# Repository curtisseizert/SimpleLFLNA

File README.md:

# SimpleLFLNA

This project contains design files for a low-frequency (0.1 - 10 Hz), AC-coupled low noise amplifier intended for measuring noise of voltage references, low noise linear supplies, etc. A number of other designs utilize input high pass filters with large (1 - 2.2 mF) electrolytic capacitors and low (ca. 1 k) resistors, this approach suffers from several drawbacks. Electrolytic capacitors exhibit high levels of dielectric absorption, leading to long settling times. Leakage can also be problematic and requires selection of parts to ensure that the amplifier does not saturate when DC bias is applied. Moreover, measurements of sources like unbuffered DAC outputs suffers from considerable input signal attenuation due to low input impedance in the passband. This design instead utilizes a much smaller (4.7 uF) polypropylene AC-coupling capacitor and large (10M) resistor with a hybrid JFET input amplifier to remove the DC bias from the signal of interest. Dielectric absorption and leakage for polypropylene capacitors is much lower than that of Al electrolytics, allowing faster settling and obviating part selection.

While this amplifier is yet to be built and tested, the design concept borrows heavily from another project (https://github.com/curtisseizert/LowFreqLNA). That project was aimed at lowest possible noise and greatest bandwidth, with different gain and bandwidth options accessible via front panel switches, but the resulting complexity, part count, and cost were relatively high for a DIY project. This project is a simpler and less expensive version with fixed gain and bandwidth. The board is a 4-layer 120x78 mm PCB designed to fit in a Hammond 1455K1201 enclosure. The amplifier can be powered by two 9V batteries or an external power source. The "settle" switch, which discharges the interstage HP filter capacitors and saturation indicator are reasonably simple quality of life features that were maintained from the more complex version. The expected noise floor is about 60-75 nV p-p depending upon some parts choices noted in the schematic. BOM cost is ca. $75 from Digikey.

I will update this repository with testing results once I have built a prototype.

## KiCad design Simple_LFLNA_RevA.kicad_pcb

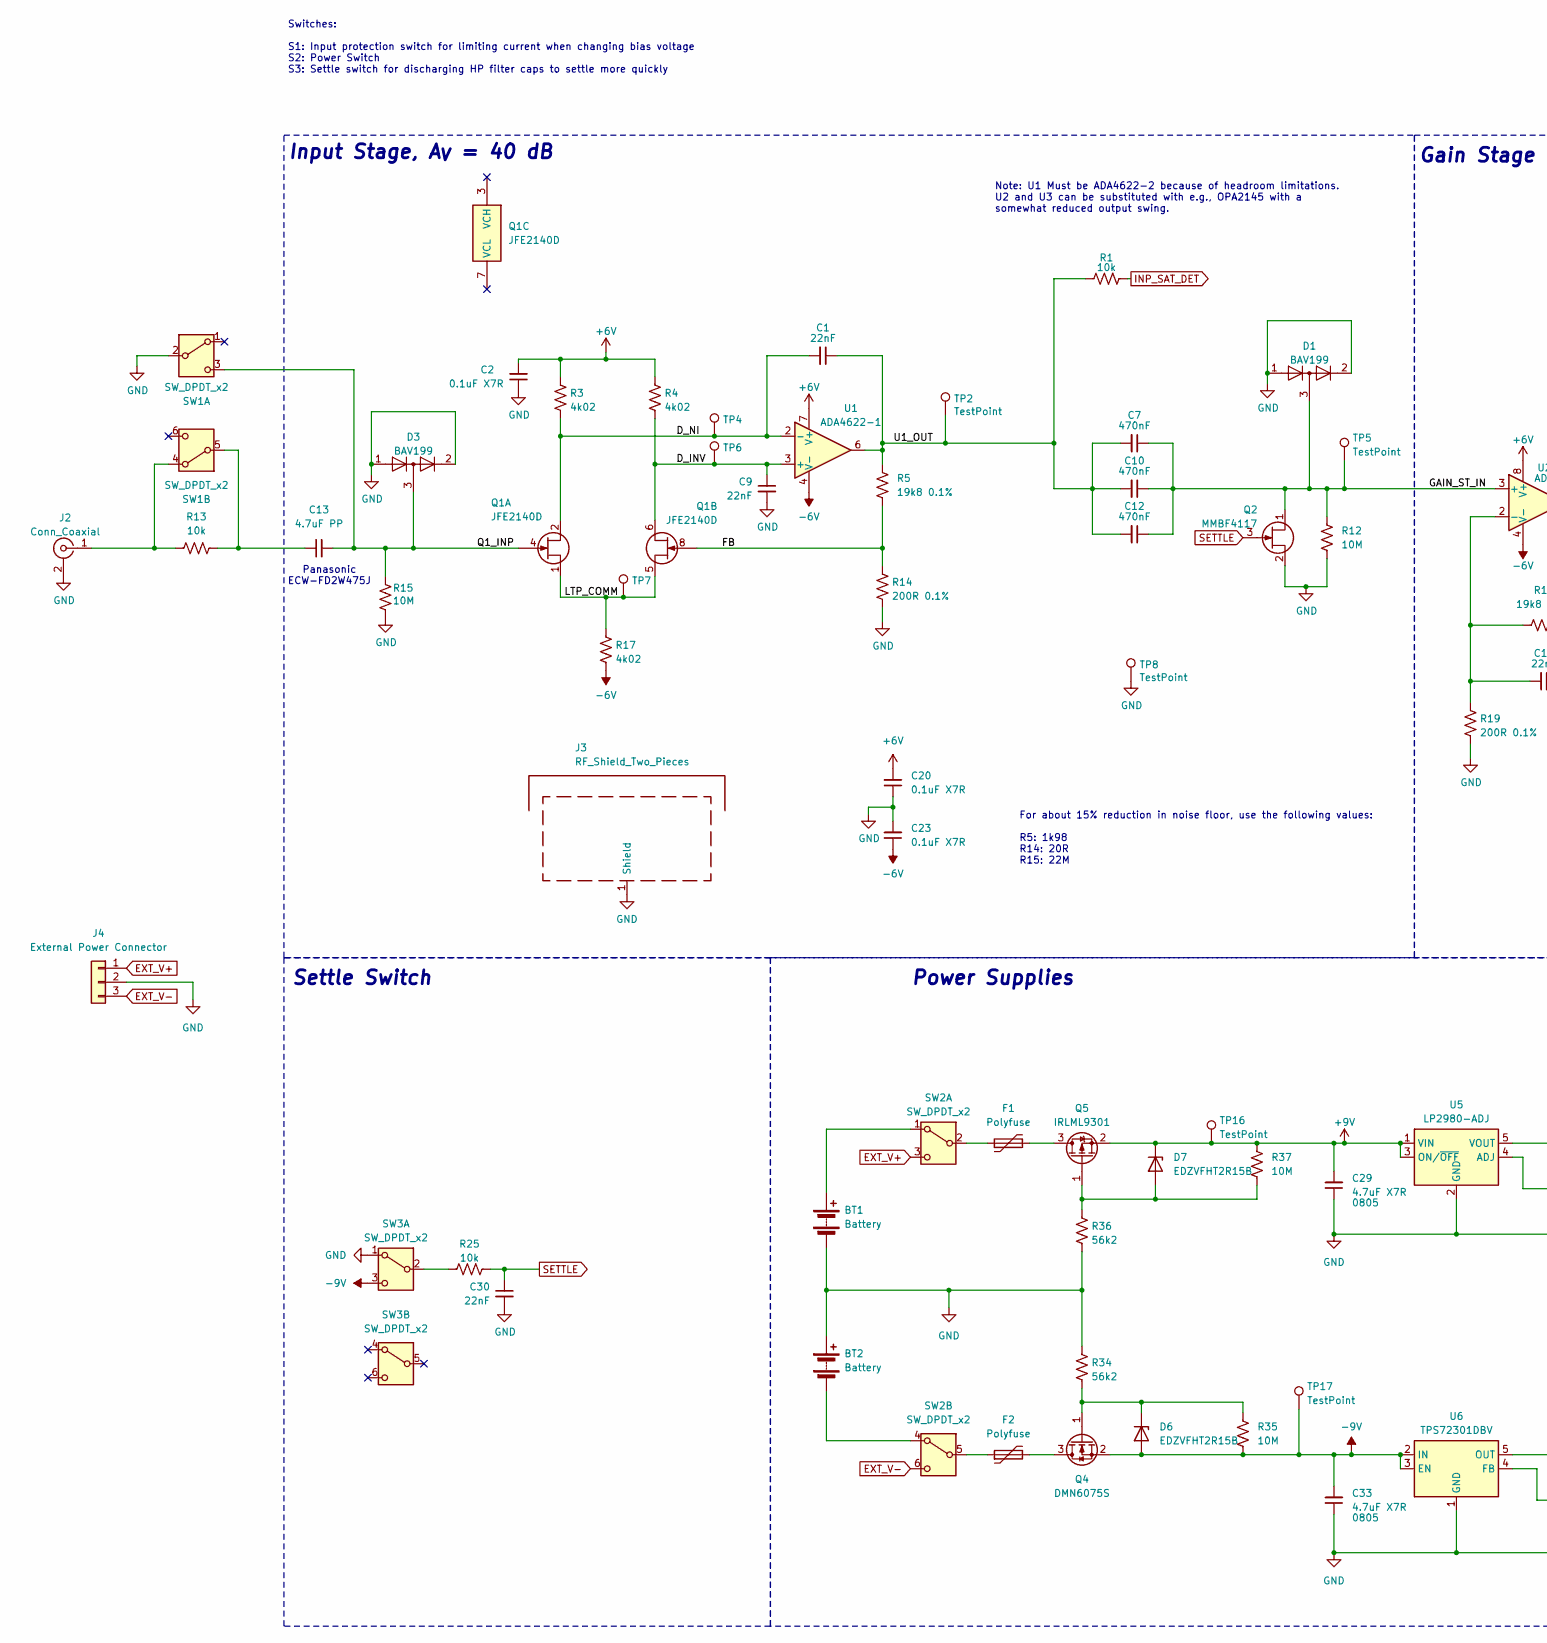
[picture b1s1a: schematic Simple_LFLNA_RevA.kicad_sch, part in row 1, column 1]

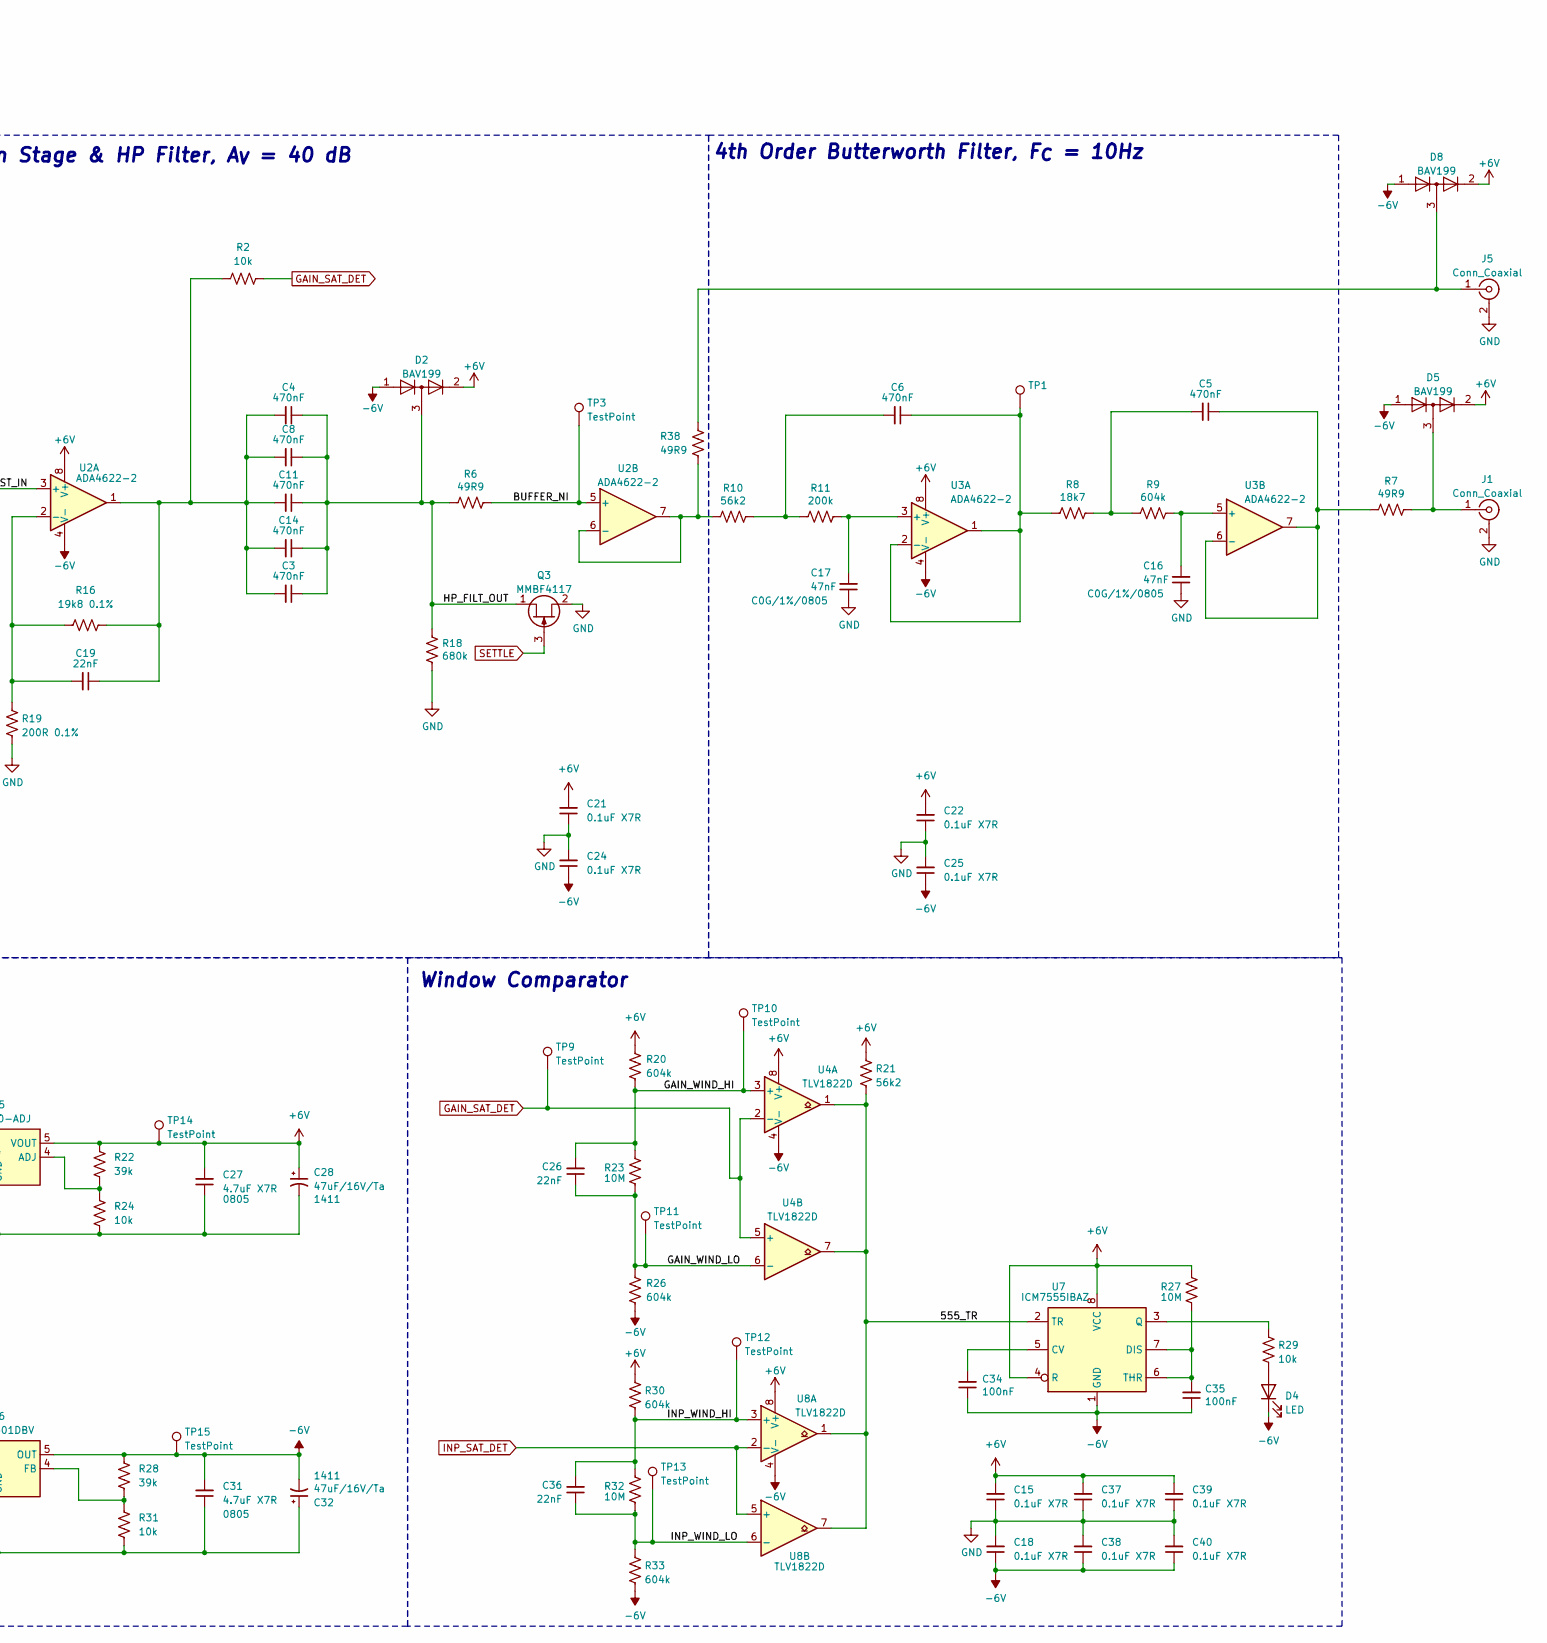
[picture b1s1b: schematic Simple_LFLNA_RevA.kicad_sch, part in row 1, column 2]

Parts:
BT1, BT2: Battery; BatteryHolder_MPD_BA9VPC_1xPP3; Digikey Price 2.42
C1, C9, C19, C26, C30, C36: 22nF; C_1206_3216Metric; Digikey Price 0.35
C2, C15, C18, C20, C21, C22, C23, C24, C25, C37, C38, C39, C40: 0.1uF X7R; C_0603_1608Metric; Digikey Price 0.072
C3, C4, C5, C6, C7, C8, C10, C11, C12, C14: 470nF; C_1206_3216Metric; Digikey Price 0.429
C13: 4.7uF PP; C_Rect_L24.0mm_W10.9mm_P22.50mm_MKT; Digikey Price 1.63
C16, C17: 47nF; C_0805_2012Metric; Digikey Price 0.31
C27, C29, C31, C33: 4.7uF X7R; C_0805_2012Metric; Digikey Price 0.25
C28, C32: 47uF/16V/Ta; CP_EIA-3528-21_Kemet-B; Digikey Price 0.75
C34, C35: 100nF; C_1206_3216Metric; Digikey Price 0.35
D1, D2, D3, D5, D8: BAV199; SOT-23; Digikey Price 0.07
D4: LED; LED_Dialight_591; Digikey Price 1.98
D6, D7: EDZVFHT2R15B; D_SOD-523; Digikey Price 0.18
F1, F2: Polyfuse; Fuse_1206_3216Metric; Digikey Price 0.17
J1, J2, J5: Conn_Coaxial; BNC_Amphenol_B6252HB-NPP3G-50_Horizontal; Digikey Price 2.05
J3: RF_Shield_Two_Pieces; Laird_Technologies_BMI-S-209-F_29.36x18.50mm; Mouser P/N 739-BMI-S-206-F
J4: External Power Connector; PinHeader_1x03_P2.54mm_Vertical
Q1: JFE2140D; SOIC-8_3.9x4.9mm_P1.27mm; Digikey Price 4.64
Q2, Q3: MMBF4117; SOT-23; Digikey Price 0.56
Q4: DMN6075S; SOT-23; Digikey Price 0.34
Q5: IRLML9301; SOT-23; Digikey Price 0.43
R1, R2, R13, R24, R25, R29, R31: 10k; R_0603_1608Metric
R3, R4, R17: 4k02; R_0603_1608Metric
R5, R16: 19k8 0.1%; R_0603_1608Metric
R6, R7, R38: 49R9; R_0603_1608Metric
R8: 18k7; R_0603_1608Metric; Mouser P/N 754-RR0816P-1872D27C
R9: 604k; R_0603_1608Metric; Mouser P/N 603-RT0603DRE07604KL
R10, R21, R34, R36: 56k2; R_0603_1608Metric; Mouser P/N 754-RR0816P-5622D73C
R11: 200k; R_0603_1608Metric; Mouser P/N 754-RR0816P-204D
R12, R15, R23, R27, R32, R35, R37: 10M; R_0603_1608Metric
R14, R19: 200R 0.1%; R_0603_1608Metric
R18: 680k; R_0603_1608Metric
R20, R26, R30, R33: 604k; R_0603_1608Metric
R22, R28: 39k; R_0603_1608Metric
SW1, SW2, SW3: SW_DPDT_x2; SW_DPDT_E-Switch_100DP1T2B4M7QE; Digikey Price 5.17
TP1, TP2, TP3, TP4, TP5, TP6, TP7, TP8, TP9, TP10, TP11, TP12, TP13, TP14, TP15, TP16, TP17: TestPoint; TestPoint_Pad_D1.0mm
U1: ADA4622-1; SOIC-8_3.9x4.9mm_P1.27mm; Digikey Price 5.88
U2, U3: ADA4622-2; SOIC-8_3.9x4.9mm_P1.27mm; Digikey Price 8.17
U4, U8: TLV1822D; SOIC-8_3.9x4.9mm_P1.27mm; Digikey Price 1.89
U5: LP2980-ADJ; SOT-23-5; Digikey Price 0.76
U6: TPS72301DBV; SOT-23-5; Digikey Price 3.80
U7: ICM7555IBAZ; SOIC-8_3.9x4.9mm_P1.27mm; Mouser P/N 700-ICM7555ISAT

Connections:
+6V: C2.2, C15.2, C20.2, C21.2, C22.2, C27.2, C28.1, C37.2, C39.2, D2.2 (A), D5.2 (A), D8.2 (A), R3.1, R4.1, R20.1, R21.1, R22.2, R27.1, R30.1, TP14.1, U1.7 (V+), U2.8 (V+), U3.8 (V+), U4.8 (V+), U5.5 (VOUT), U7.4 (R), U7.8 (VCC), U8.8 (V+)
+9V: C29.2, D7.1 (K), Q5.2 (S), R37.1, TP16.1, U5.1 (VIN), U5.3 (ON/~OFF)
-6V: C18.1, C23.1, C24.1, C25.1, C31.2, C32.2, C34.1, C35.1, C38.1, C40.1, D2.1 (K), D4.1 (K), D5.1 (K), D8.1 (K), R17.2, R26.2, R28.2, R33.2, TP15.1, U1.4 (V-), U2.4 (V-), U3.4 (V-), U4.4 (V-), U6.5 (OUT), U7.1 (GND), U8.4 (V-)
-9V: C33.2, D6.2 (A), Q4.2 (S), R35.2, SW3.3 (C), TP17.1, U6.2 (IN), U6.3 (EN)
/555_TR: R21.2, U4.1, U4.7, U7.2 (TR), U8.1, U8.7
/BUFFER_NI: R6.1, TP3.1, U2.5 (+)
/D_INV: C9.1, Q1.6, R4.2, TP6.1, U1.3 (+)
/D_NI: C1.2, Q1.2, R3.2, TP4.1, U1.2 (-)
/FB: Q1.8, R5.1, R14.1
/GAIN_ST_IN: C7.1, C10.1, C12.1, D1.3 (K), Q2.1 (D), R12.1, TP5.1, U2.3 (+)
/GAIN_WIND_HI: C26.2, R20.2, R23.1, TP10.1, U4.3 (+)
/GAIN_WIND_LO: C26.1, R23.2, R26.1, TP11.1, U4.6 (-)
/HP_FILT_OUT: C3.1, C4.1, C8.1, C11.1, C14.1, D2.3 (K), Q3.1 (D), R6.2, R18.1
/INP_WIND_HI: C36.2, R30.2, R32.1, TP12.1, U8.3 (+)
/INP_WIND_LO: C36.1, R32.2, R33.1, TP13.1, U8.6 (-)
/LTP_COMM: Q1.1, Q1.5, R17.1, TP7.1
/Q1_INP: C13.2, D3.3 (K), Q1.4, R15.1, SW1.3 (C)
/U1_OUT: C1.1, C7.2, C10.2, C12.2, R1.1, R5.2, TP2.1, U1.6
EXT_V+: J4.1, SW2.3 (C)
EXT_V-: J4.3, SW2.6 (C)
GAIN_SAT_DET: R2.2, TP9.1, U4.2 (-), U4.5 (+)
GND: BT1.2 (-), BT2.1 (+), C2.1, C9.2, C15.1, C16.1, C17.1, C18.2, C20.1, C21.1, C22.1, C23.2, C24.2, C25.2, C27.1, C28.2, C29.1, C30.2, C31.1, C32.1, C33.1, C37.1, C38.2, C39.1, C40.2, D1.1 (K), D1.2 (A), D3.1 (K), D3.2 (A), J1.2 (Ext), J2.2 (Ext), J3.1 (Shield), J4.2, J5.2 (Ext), Q2.2 (S), Q3.2 (S), R12.2, R14.2, R15.2, R18.2, R19.2, R24.2, R31.2, R34.1, R36.2, SW1.2 (B), SW3.1 (A), TP8.1, U5.2 (GND), U6.1 (GND)
INP_SAT_DET: R1.2, U8.2 (-), U8.5 (+)
unnamed: BT1.1 (+), SW2.1 (A)
unnamed: BT2.2 (-), SW2.4 (A)
unnamed: C5.2, R8.1, R9.2
unnamed: C6.2, R10.1, R11.2
unnamed: C3.2, C4.2, C8.2, C11.2, C14.2, C19.1, R2.1, R16.2, U2.1
unnamed: D4.2 (A), R29.2
unnamed: D6.1 (K), Q4.1 (G), R34.2, R35.1
unnamed: D7.2 (A), Q5.1 (G), R36.1, R37.2
unnamed: D5.3 (K), J1.1 (In), R7.1
unnamed: J2.1 (In), R13.1, SW1.4 (A)
unnamed: D8.3 (K), J5.1 (In), R38.1
unnamed: F2.2, Q4.3 (D)
unnamed: F1.2, Q5.3 (D)
unnamed: C13.1, R13.2, SW1.5 (B)
unnamed: F1.1, SW2.2 (B)
unnamed: F2.1, SW2.5 (B)
unnamed: R25.1, SW3.2 (B)
unnamed: C19.2, R16.1, R19.1, U2.2 (-)
unnamed: R10.2, R38.2, U2.6 (-), U2.7
unnamed: C17.2, R11.1, U3.3 (+)
unnamed: C6.1, R8.2, TP1.1, U3.1, U3.2 (-)
unnamed: C16.2, R9.1, U3.5 (+)
unnamed: C5.1, R7.2, U3.6 (-), U3.7
unnamed: R22.1, R24.1, U5.4 (ADJ)
unnamed: R28.1, R31.1, U6.4 (FB)
unnamed: C34.2, U7.5 (CV)
unnamed: C35.2, R27.2, U7.6 (THR), U7.7 (DIS)
unnamed: R29.1, U7.3 (Q)
SETTLE: C30.1, Q2.3 (G), Q3.3 (G), R25.2

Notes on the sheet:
Panasonic ECW-FD2W475J
Input Stage, A_{V} = 40 dB
Switches: S1: Input protection switch for limiting current when changing bias voltage S2: Power Switch S3: Settle switch for discharging HP filter caps to settle more quickly
For about 15% reduction in noise floor, use the following values: R5: 1k98 R14: 20R R15: 22M
Power Supplies
4th Order Butterworth Filter, F_{C} = 10Hz
Note: U1 Must be ADA4622-2 because of headroom limitations. U2 and U3 can be substituted with e.g., OPA2145 with a somewhat reduced output swing.
Window Comparator
Settle Switch
Gain Stage & HP Filter, A_{V} = 40 dB

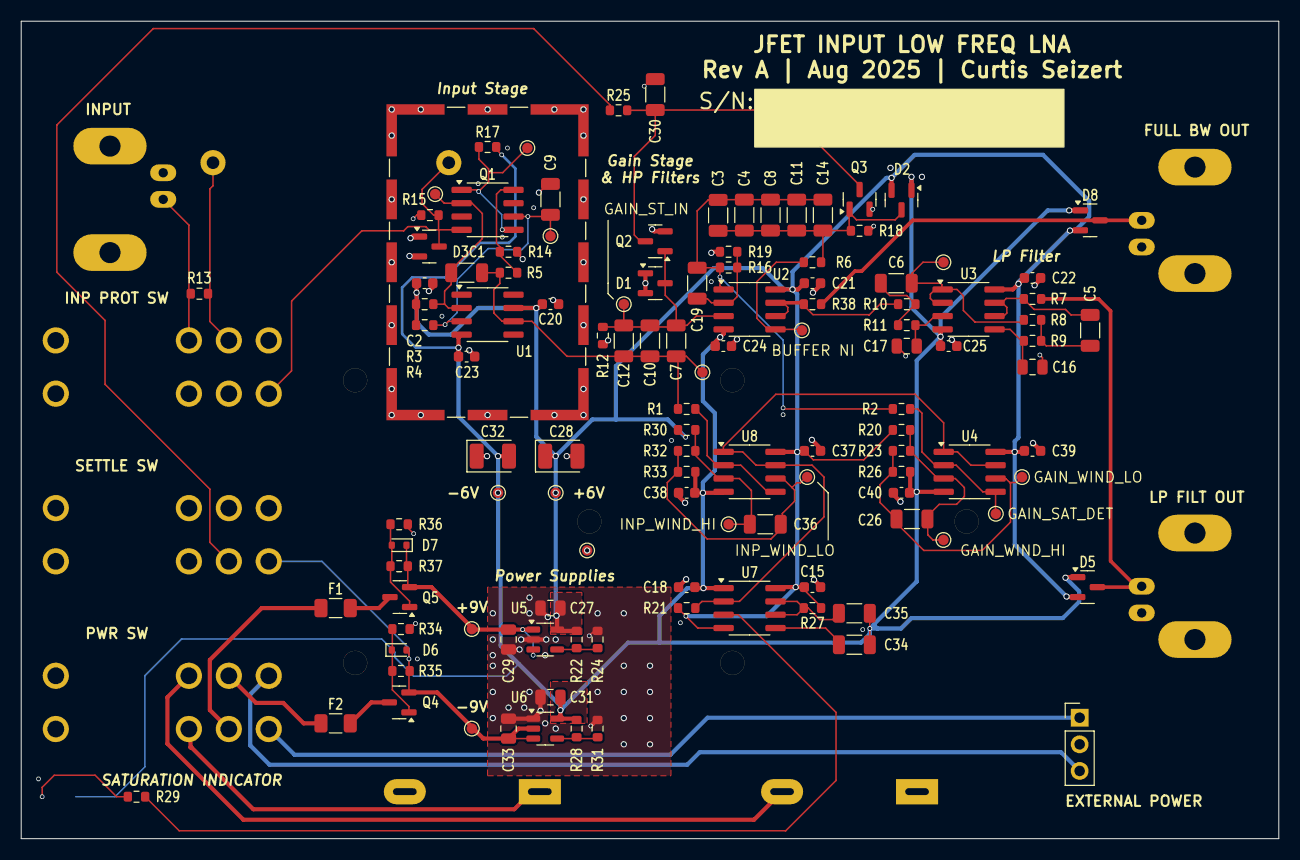
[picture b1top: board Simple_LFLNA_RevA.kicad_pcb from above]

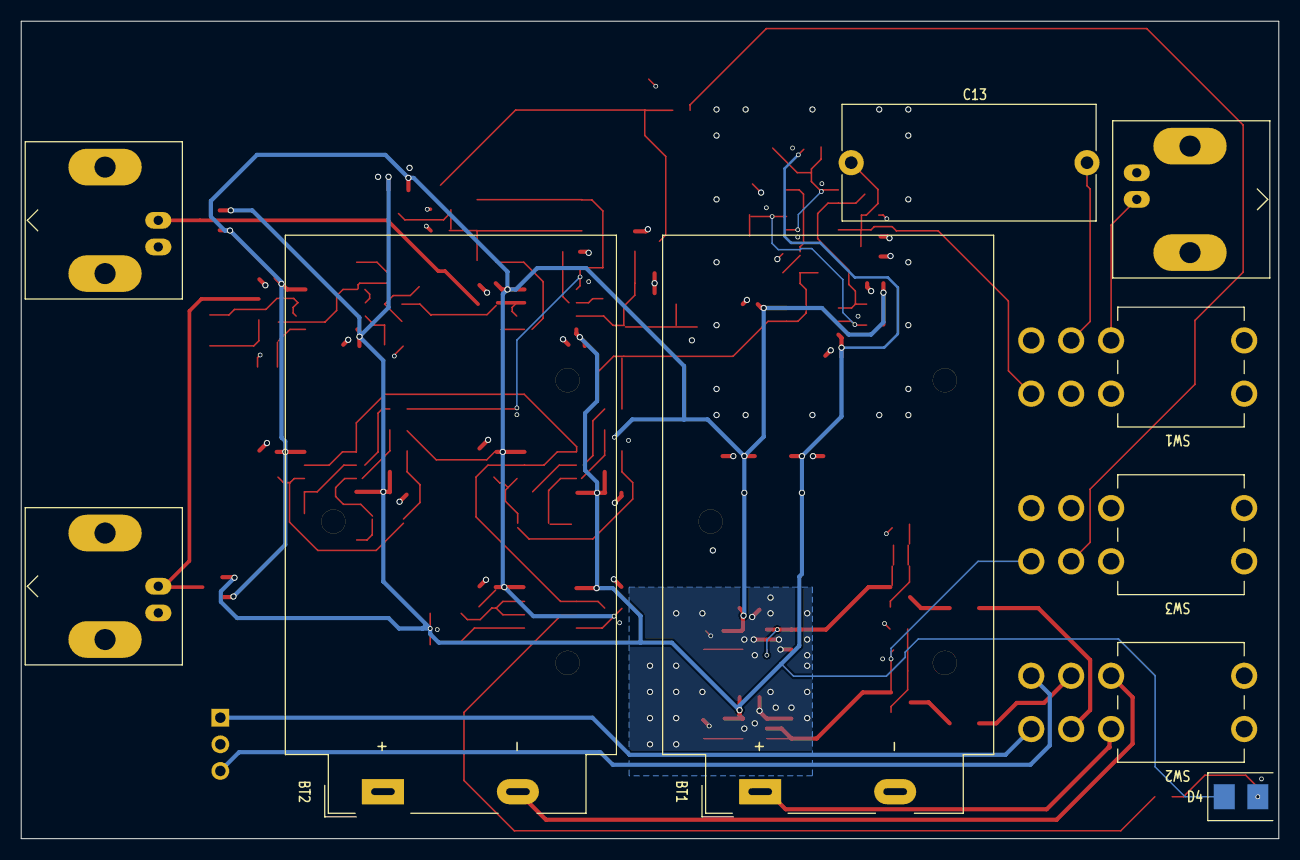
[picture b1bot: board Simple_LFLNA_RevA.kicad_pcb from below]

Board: 4 copper layers, 120.0 x 78.0 mm, 128 parts (10 on the bottom side), 52 nets.

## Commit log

2025-08-29 Update README.md
    Added 3D board render
